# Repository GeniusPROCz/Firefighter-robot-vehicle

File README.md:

🧑‍🚒 Firefighter Robot Vehicle

Autor / Author: Jan Suttner (alias GeniusPROCz)
Rok / Year: © 2025
Verze licence / License Version: 1.0 — Custom Non-Commercial License

🛡️ Právní upozornění / Legal Notice

Tento projekt, včetně všech svých současných i budoucích částí (software, firmware, schémata, návrhy PCB, 3D modely, dokumentace, texty a obrázky), je chráněn autorským právem podle zákona č. 121/2000 Sb. (CZ) a mezinárodních úmluv (Berne Convention).
Použitím, kopírováním, úpravou nebo sdílením tohoto díla souhlasíš s níže uvedenými licenčními podmínkami.
Pokud s nimi nesouhlasíš, nemáš právo projekt nebo jeho části jakkoli používat, upravovat ani šířit.

📘 Tento projekt podléhá licenčním podmínkám uvedeným v sekci „📜 Licenční podmínky / License & Usage Terms“ níže.

📜 Licenční podmínky / License & Usage Terms

Autor / Author: Jan Suttner (GeniusPROCz)
Projekt / Project: Firefighter Robot Vehicle
Licence / License: Custom Non-Commercial License
Komerční použití / Commercial Use: Pouze po písemné dohodě s autorem / Only with author’s written consent

🇨🇿 Česká verze (právně závazná v ČR)

Autor uděluje uživatelům následující oprávnění:

✅ Povolené použití

Používat, upravovat a sdílet tento projekt pro osobní, vzdělávací a nekomerční účely.

Prezentovat nebo forkovat projekt za předpokladu zachování uvedení autora:

© 2025 Jan Suttner (GeniusPROCz) — originální projekt: https://github.com/GeniusPROCz/Firefighter-Robot-Vehicle

🚫 Zakázané použití

Jakékoli komerční využití (prodej, výroba, reklama, monetizace, placené služby atd.) bez písemného souhlasu autora.

Přivlastnění si autorství, úprava či odstranění označení původního autora.

Šíření bez tohoto licenčního textu nebo bez odkazu na původní repozitář.

⚙️ Shrnutí práv
Právo	Stav
Osobní / vzdělávací použití	✅ Povoleno
Úpravy a sdílení (s uvedením autora)	✅ Povoleno
Komerční použití	⚠️ Pouze po písemné dohodě s autorem
Přivlastnění / šíření bez zdroje	❌ Zakázáno
⚠️ Prohlášení

Projekt je poskytován „tak, jak je“ (as is) bez jakékoli záruky. Autor nenese odpovědnost za škody vzniklé použitím nebo modifikací materiálů.

🇬🇧 English Version (internationally equivalent)

The author grants the following permissions:

✅ Allowed

Use, modify and share this project for personal, educational and non-commercial purposes.

Publicly present or fork this repository with proper credit to the author:

© 2025 Jan Suttner (GeniusPROCz) — original project: https://github.com/GeniusPROCz/Firefighter-Robot-Vehicle

🚫 Prohibited

Any commercial use (sales, production, advertising, monetization, paid services, etc.) without prior written consent from the author.

Removing or altering author attribution.

Redistributing this work without this license text or a link to the original repository.

⚙️ Rights Summary
Right	Status
Personal / educational use	✅ Allowed
Modification & redistribution (with credit)	✅ Allowed
Commercial use	⚠️ Only with written permission
Misattribution / uncredited redistribution	❌ Forbidden
⚠️ Disclaimer

This project is provided “as is”, without any warranty of any kind. The author shall not be liable for any damages arising from use or modification.

✅ Použitím tohoto repozitáře výslovně souhlasíš s výše uvedenými podmínkami.
Jakékoli komerční použití bez souhlasu autora může být považováno za porušení autorských práv (§ 12 a násl. zákona č. 121/2000 Sb.).

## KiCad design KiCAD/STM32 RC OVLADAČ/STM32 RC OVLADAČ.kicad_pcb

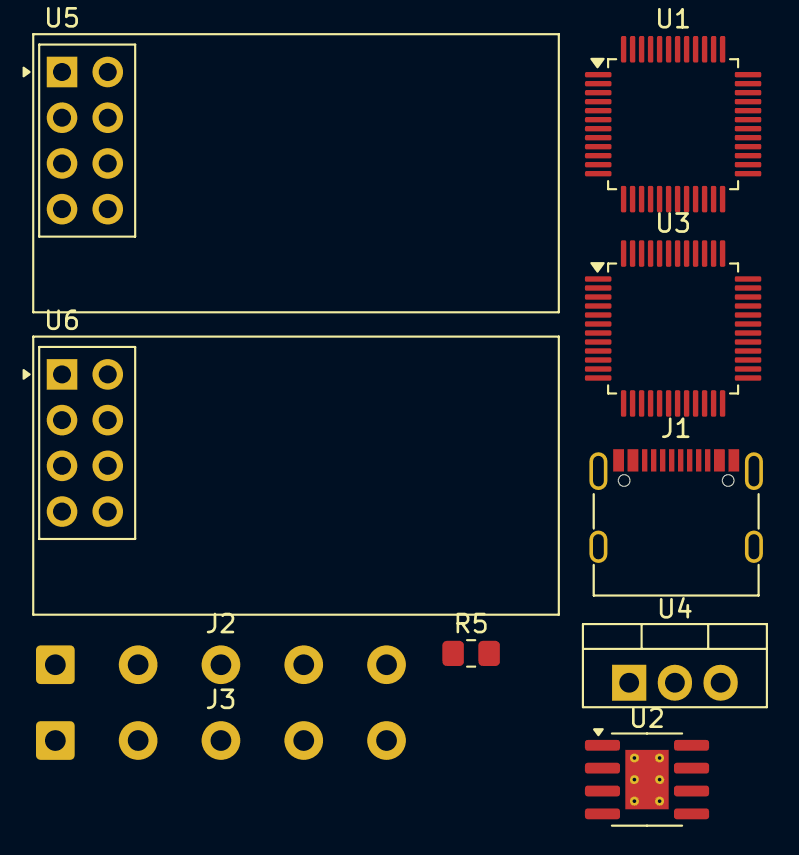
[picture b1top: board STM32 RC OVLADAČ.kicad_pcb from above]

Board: 2 copper layers, 10 parts (0 on the bottom side), 7 nets, no tracks yet.

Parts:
J1: USB_C_Receptacle_USB2.0_16P; USB_C_Receptacle_G-Switch_GT-USB-7010ASV_model
J2, J3: Conn_01x05_Socket; SolderWire-0.5sqmm_1x05_P4.6mm_D0.9mm_OD2.1mm
R5: R; R_0805_2012Metric_Pad1.20x1.40mm_HandSolder
U1, U3: STM32F030C8Tx; LQFP-48_7x7mm_P0.5mm
U2: TP4056-42-ESOP8; SOIC-8-1EP_3.9x4.9mm_P1.27mm_EP2.41x3.3mm_ThermalVias_model
U4: LD1117V33; TO-220-3_Vertical
U5, U6: NRF24L01_Breakout; nRF24L01_Breakout

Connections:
+3.3V: U1.1 (VDD), U1.9 (VDDA), U1.24 (VDD), U1.48 (VDD), U3.1 (VDD), U3.24 (VDD), U3.48 (VDD), U4.2 (VO), U5.2 (VCC), U6.2 (VCC)
GND: J1.A1 (GND), J1.A12 (GND), J1.B1 (GND), J1.B12 (GND), J1.S1 (SHIELD), J2.5, J3.5, R5.2, U1.8 (VSSA), U1.23 (VSS), U1.47 (VSS), U2.1 (TEMP), U2.3 (GND), U2.9 (EPAD), U3.23 (VSS), U3.47 (VSS), U4.1 (GND), U5.1 (GND), U6.1 (GND)
unnamed: U2.5 (BAT), U4.3 (VI)
unnamed: J1.A4 (VBUS), J1.A9 (VBUS), J1.B4 (VBUS), J1.B9 (VBUS), U2.4 (V_{CC}), U2.8 (CE)
unnamed: U1.13 (PA3), U5.3 (CE)
unnamed: R5.1, U2.2 (PROG)
unnamed: U3.13 (PA3), U6.3 (CE)

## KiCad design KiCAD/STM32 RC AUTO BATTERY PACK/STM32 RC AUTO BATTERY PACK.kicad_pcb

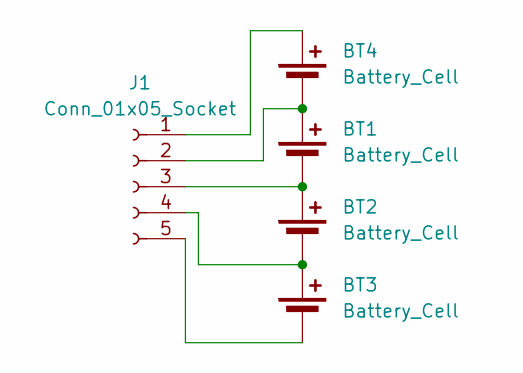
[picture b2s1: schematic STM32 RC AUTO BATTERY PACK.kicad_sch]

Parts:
BT1, BT2, BT3, BT4: Battery_Cell; 21700 laskakit battery holder
J1: Conn_01x05_Socket; JST_XH_B5B-XH-A_1x05_P2.50mm_Vertical

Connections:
unnamed: BT1.1 (+), BT4.2 (-), J1.2
unnamed: BT1.2 (-), BT2.1 (+), J1.3
unnamed: BT2.2 (-), BT3.1 (+), J1.4
unnamed: BT3.2 (-), J1.5
unnamed: BT4.1 (+), J1.1

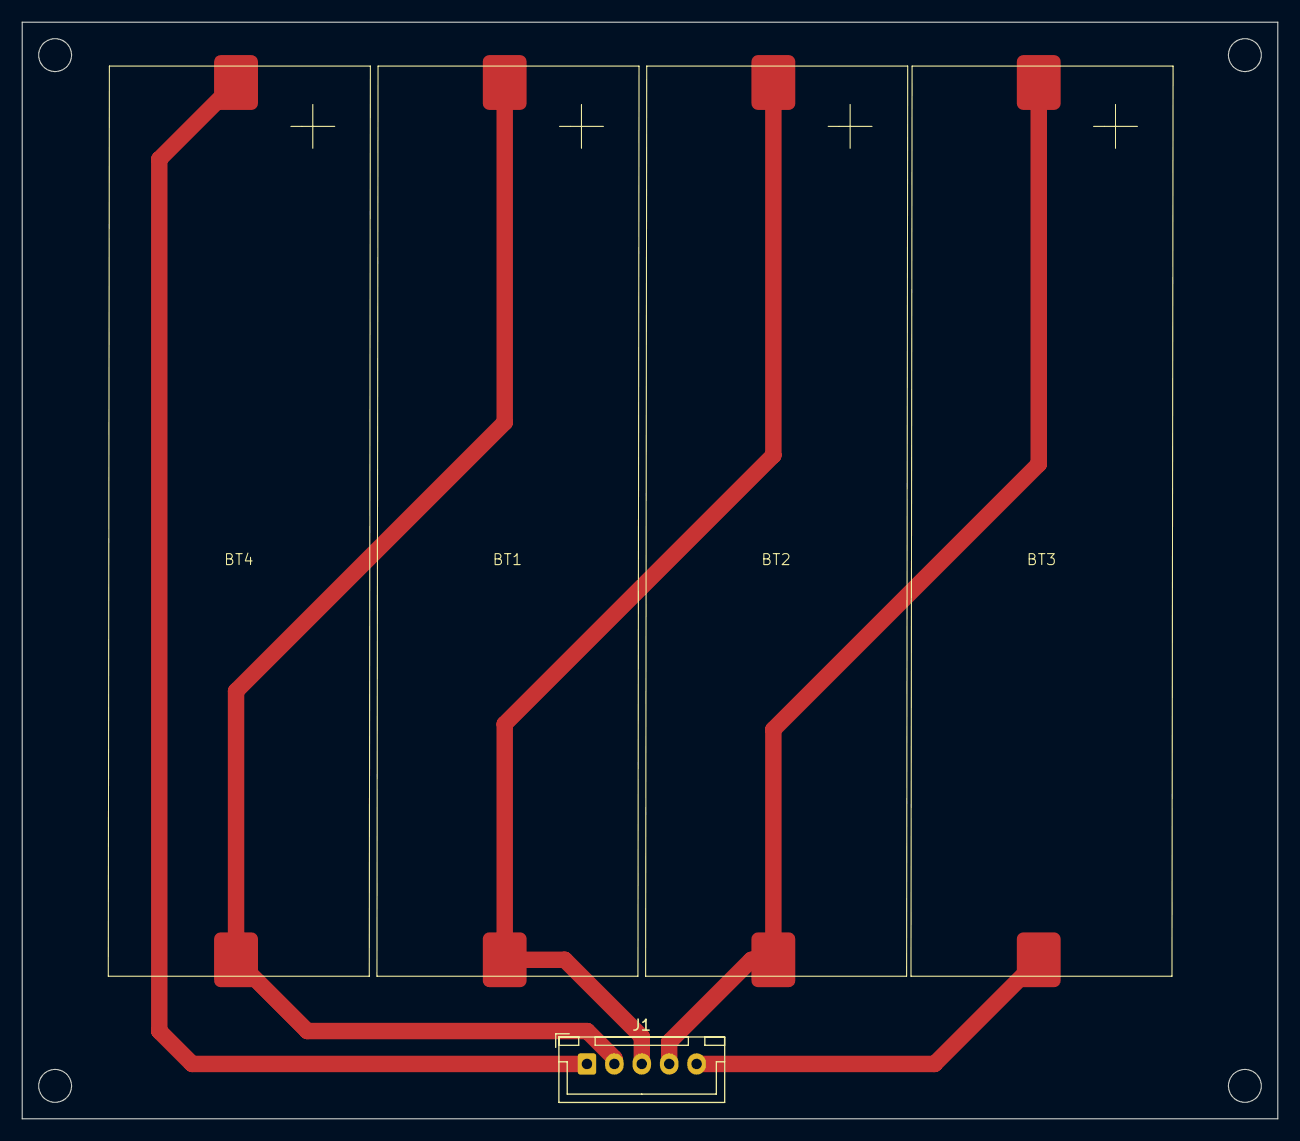
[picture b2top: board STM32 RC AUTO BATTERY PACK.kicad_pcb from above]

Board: 2 copper layers, 114.5 x 100.0 mm, 5 parts (0 on the bottom side), 5 nets.

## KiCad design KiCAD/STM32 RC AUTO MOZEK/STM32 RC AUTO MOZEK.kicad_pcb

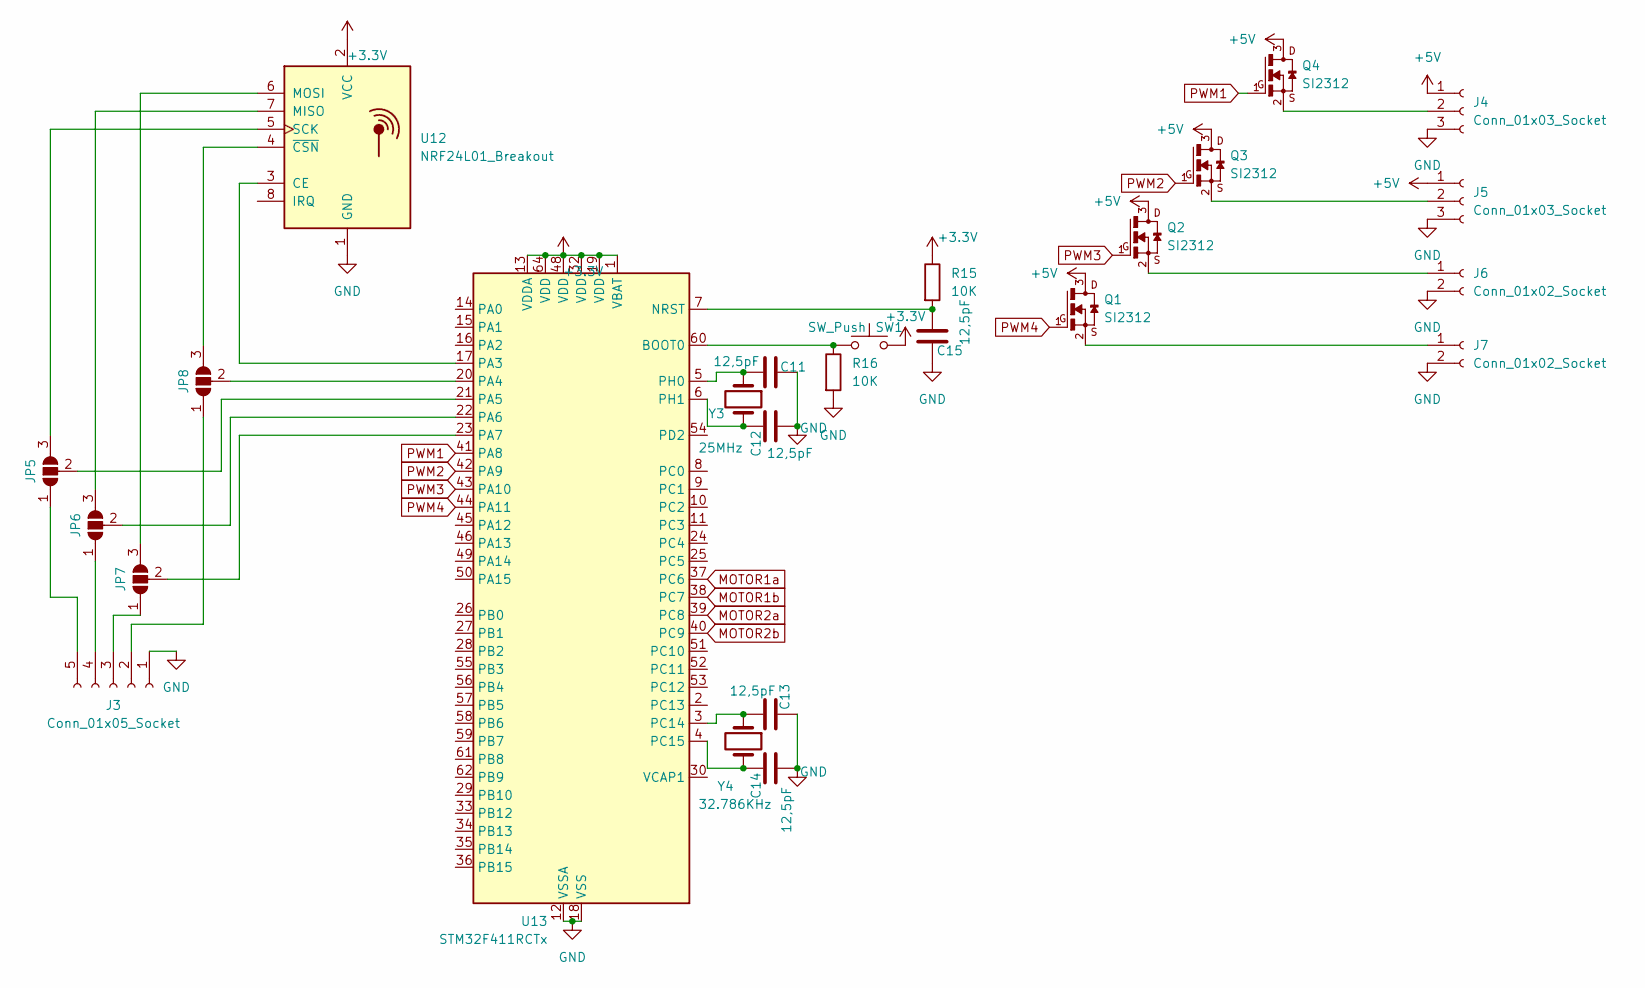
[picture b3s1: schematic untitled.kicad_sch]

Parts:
C11, C12, C13, C14, C15: 12,5pF; C_0805_2012Metric_Pad1.18x1.45mm_HandSolder
J3: Conn_01x05_Socket; SolderWire-0.5sqmm_1x05_P4.8mm_D0.9mm_OD2.3mm_Relief
J4, J5: Conn_01x03_Socket; JST_XH_B3B-XH-A_1x03_P2.50mm_Vertical
J6, J7: Conn_01x02_Socket; JST_XH_B2B-XH-A_1x02_P2.50mm_Vertical
JP5, JP6, JP7, JP8: SolderJumper_3_Open; SolderJumper-3_P1.3mm_Open_RoundedPad1.0x1.5mm_NumberLabels
Q1, Q2, Q3, Q4: SI2312; SOT23
R15, R16: 10K; R_0805_2012Metric_Pad1.20x1.40mm_HandSolder
SW1: SW_Push; SW_SPST_CK_RS282G05A3
U12: NRF24L01_Breakout; nRF24L01_Breakout
U13: STM32F411RCTx; LQFP-64_10x10mm_P0.5mm
Y3: 25MHz; Crystal_SMD_HC49-SD
Y4: 32.786KHz; Crystal_DS26_D2.0mm_L6.0mm_Horizontal

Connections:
+3.3V: R15.1, SW1.2, U12.2 (VCC), U13.1 (VBAT), U13.13 (VDDA), U13.19 (VDD), U13.32 (VDD), U13.48 (VDD), U13.64 (VDD); also elsewhere on the board
+5V: J4.1, J5.1, Q1.3, Q2.3, Q3.3, Q4.3; also elsewhere on the board
GND: C11.1, C12.2, C13.1, C14.2, C15.1, J3.1, J4.3, J5.3, J6.2, J7.2, R16.2, U12.1 (GND), U13.12 (VSSA), U13.18 (VSS), U13.31 (VSS), U13.47 (VSS), U13.63 (VSS); also elsewhere on the board
MOTOR1a: U13.37 (PC6); also elsewhere on the board
MOTOR1b: U13.38 (PC7); also elsewhere on the board
MOTOR2a: U13.39 (PC8); also elsewhere on the board
MOTOR2b: U13.40 (PC9); also elsewhere on the board
unnamed: J3.2, JP8.1 (A)
unnamed: J3.3, JP7.1 (A)
unnamed: J3.4, JP6.1 (A)
unnamed: J3.5, JP5.1 (A)
unnamed: J4.2, Q4.2
unnamed: J5.2, Q3.2
unnamed: J6.1, Q2.2
unnamed: J7.1, Q1.2
unnamed: JP5.3 (B), U12.5 (SCK)
unnamed: JP5.2 (C), U13.21 (PA5)
unnamed: JP6.3 (B), U12.7 (MISO)
unnamed: JP6.2 (C), U13.22 (PA6)
unnamed: JP7.3 (B), U12.6 (MOSI)
unnamed: JP7.2 (C), U13.23 (PA7)
unnamed: JP8.3 (B), U12.4 (~CSN)
unnamed: JP8.2 (C), U13.20 (PA4)
unnamed: U12.3 (CE), U13.17 (PA3)
unnamed: R16.1, SW1.1, U13.60 (BOOT0)
unnamed: C15.2, R15.2, U13.7 (NRST)
unnamed: C13.2, U13.3 (PC14), Y4.1
unnamed: C14.1, U13.4 (PC15), Y4.2
unnamed: C11.2, U13.5 (PH0), Y3.1
unnamed: C12.1, U13.6 (PH1), Y3.2
PWM1: Q4.1, U13.41 (PA8)
PWM2: Q3.1, U13.42 (PA9)
PWM3: Q2.1, U13.43 (PA10)
PWM4: Q1.1, U13.44 (PA11)

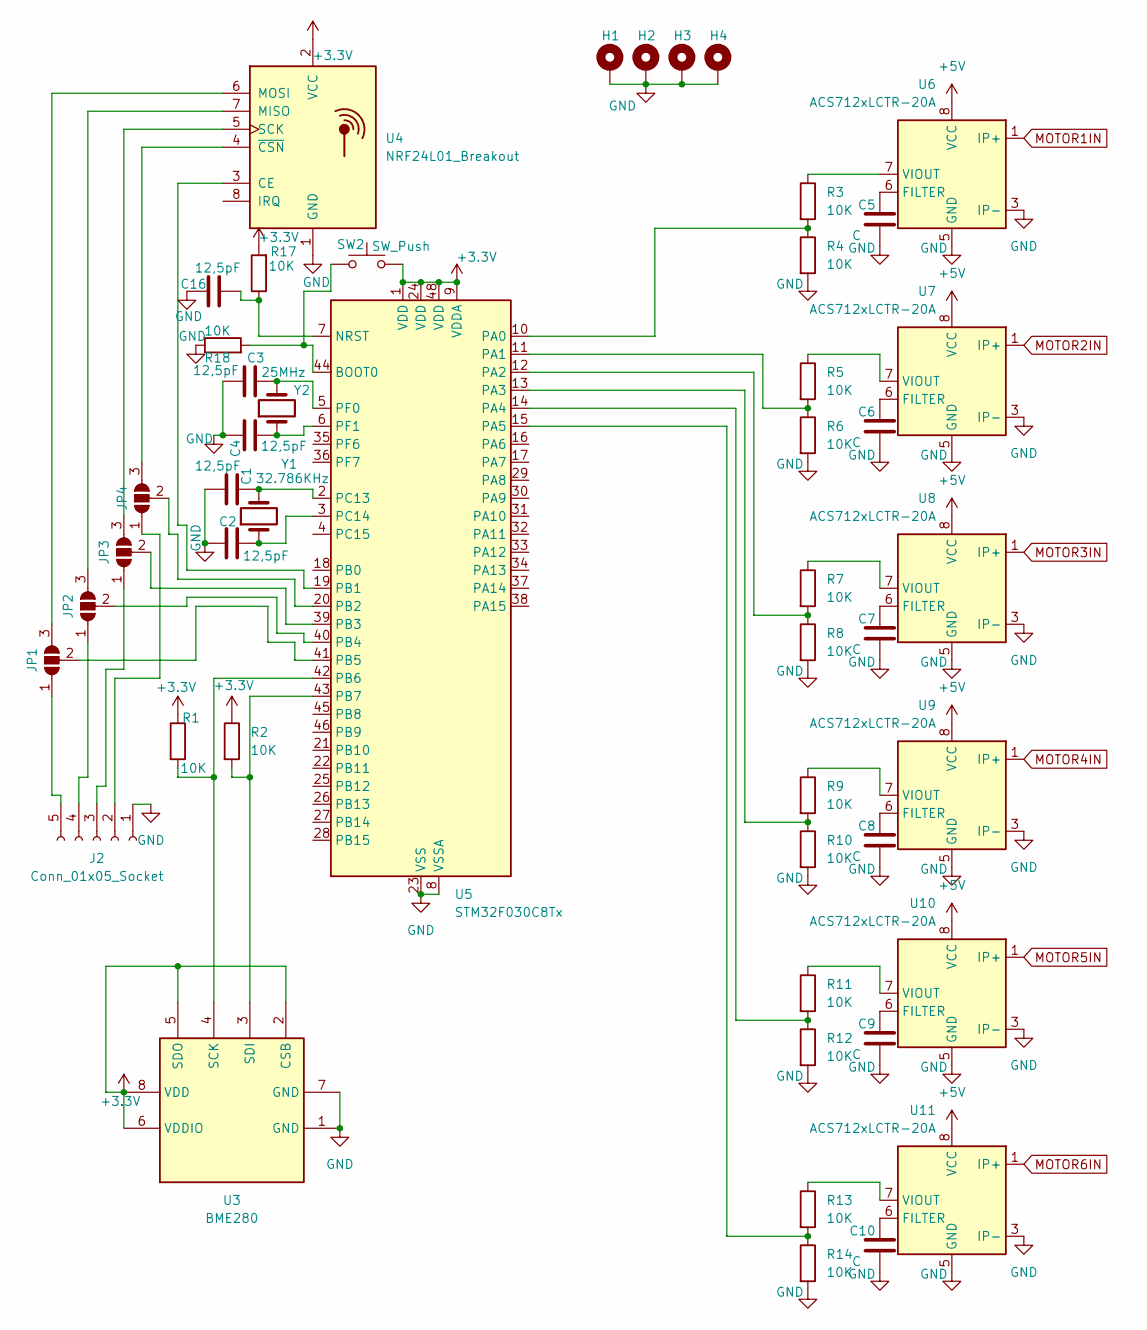
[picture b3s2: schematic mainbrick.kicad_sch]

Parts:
C1, C2, C3, C4, C16: 12,5pF; C_0805_2012Metric_Pad1.18x1.45mm_HandSolder
C5, C6, C7, C8, C9, C10: C; C_0805_2012Metric_Pad1.18x1.45mm_HandSolder
H1, H2, H3, H4: MountingHole_Pad; MountingHole_3.5mm_Pad_Via
J2: Conn_01x05_Socket; SolderWire-0.5sqmm_1x05_P4.8mm_D0.9mm_OD2.3mm_Relief
JP1, JP2, JP3, JP4: SolderJumper_3_Open; SolderJumper-3_P1.3mm_Open_RoundedPad1.0x1.5mm_NumberLabels
R1, R2, R3, R4, R5, R6, R7, R8, R9, R10, R11, R12, R13, R14, R17, R18: 10K; R_0805_2012Metric_Pad1.20x1.40mm_HandSolder
SW2: SW_Push; SW_SPST_CK_RS282G05A3
U3: BME280; Bosch_LGA-8_2.5x2.5mm_P0.65mm_ClockwisePinNumbering
U4: NRF24L01_Breakout; nRF24L01_Breakout
U5: STM32F030C8Tx; LQFP-48_7x7mm_P0.5mm
U6, U7, U8, U9, U10, U11: ACS712xLCTR-20A; SOIC-8_3.9x4.9mm_P1.27mm
Y1: 32.786KHz; Crystal_DS26_D2.0mm_L6.0mm_Horizontal
Y2: 25MHz; Crystal_SMD_HC49-SD

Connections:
+3.3V: R1.1, R2.1, R17.2, SW2.2, U3.2 (CSB), U3.5 (SDO), U3.6 (VDDIO), U3.8 (VDD), U4.2 (VCC), U5.1 (VDD), U5.9 (VDDA), U5.24 (VDD), U5.48 (VDD); also elsewhere on the board
+5V: U6.8 (VCC), U7.8 (VCC), U8.8 (VCC), U9.8 (VCC), U10.8 (VCC), U11.8 (VCC); also elsewhere on the board
GND: C1.2, C2.1, C3.2, C4.1, C5.2, C6.2, C7.2, C8.2, C9.2, C10.2, C16.2, H1.1, H2.1, H3.1, H4.1, J2.1, R4.2, R6.2, R8.2, R10.2, R12.2, R14.2, R18.1, U3.1 (GND), U3.7 (GND), U4.1 (GND), U5.8 (VSSA), U5.23 (VSS), U5.47 (VSS), U6.3 (IP-), U6.4 (IP-), U6.5 (GND), U7.3 (IP-), U7.4 (IP-), U7.5 (GND), U8.3 (IP-), U8.4 (IP-), U8.5 (GND), U9.3 (IP-), U9.4 (IP-), U9.5 (GND), U10.3 (IP-), U10.4 (IP-), U10.5 (GND), U11.3 (IP-), U11.4 (IP-), U11.5 (GND); also elsewhere on the board
MOTOR1IN: U6.1 (IP+), U6.2 (IP+); also elsewhere on the board
MOTOR2IN: U7.1 (IP+), U7.2 (IP+); also elsewhere on the board
MOTOR3IN: U8.1 (IP+), U8.2 (IP+); also elsewhere on the board
MOTOR4IN: U9.1 (IP+), U9.2 (IP+); also elsewhere on the board
MOTOR5IN: U10.1 (IP+), U10.2 (IP+); also elsewhere on the board
MOTOR6IN: U11.1 (IP+), U11.2 (IP+); also elsewhere on the board
unnamed: J2.2, JP4.1 (A)
unnamed: J2.3, JP3.1 (A)
unnamed: J2.4, JP2.1 (A)
unnamed: J2.5, JP1.1 (A)
unnamed: JP1.3 (B), U4.6 (MOSI)
unnamed: JP1.2 (C), U5.41 (PB5)
unnamed: JP2.3 (B), U4.7 (MISO)
unnamed: JP2.2 (C), U5.40 (PB4)
unnamed: JP3.3 (B), U4.5 (SCK)
unnamed: JP3.2 (C), U5.39 (PB3)
unnamed: JP4.3 (B), U4.4 (~CSN)
unnamed: JP4.2 (C), U5.20 (PB2)
unnamed: R1.2, U3.4 (SCK), U5.42 (PB6)
unnamed: R2.2, U3.3 (SDI), U5.43 (PB7)
unnamed: U4.3 (CE), U5.19 (PB1)
unnamed: R18.2, SW2.1, U5.44 (BOOT0)
unnamed: C16.1, R17.1, U5.7 (NRST)
unnamed: R3.2, R4.1, U5.10 (PA0)
unnamed: R5.2, R6.1, U5.11 (PA1)
unnamed: R7.2, R8.1, U5.12 (PA2)
unnamed: R9.2, R10.1, U5.13 (PA3)
unnamed: R11.2, R12.1, U5.14 (PA4)
unnamed: R13.2, R14.1, U5.15 (PA5)
unnamed: C1.1, U5.2 (PC13), Y1.2
unnamed: C2.2, U5.3 (PC14), Y1.1
unnamed: C3.1, U5.5 (PF0), Y2.2
unnamed: C4.2, U5.6 (PF1), Y2.1
unnamed: C5.1, U6.6 (FILTER)
unnamed: R3.1, U6.7 (VIOUT)
unnamed: C6.1, U7.6 (FILTER)
unnamed: R5.1, U7.7 (VIOUT)
unnamed: C7.1, U8.6 (FILTER)
unnamed: R7.1, U8.7 (VIOUT)
unnamed: C8.1, U9.6 (FILTER)
unnamed: R9.1, U9.7 (VIOUT)
unnamed: C9.1, U10.6 (FILTER)
unnamed: R11.1, U10.7 (VIOUT)
unnamed: C10.1, U11.6 (FILTER)
unnamed: R13.1, U11.7 (VIOUT)

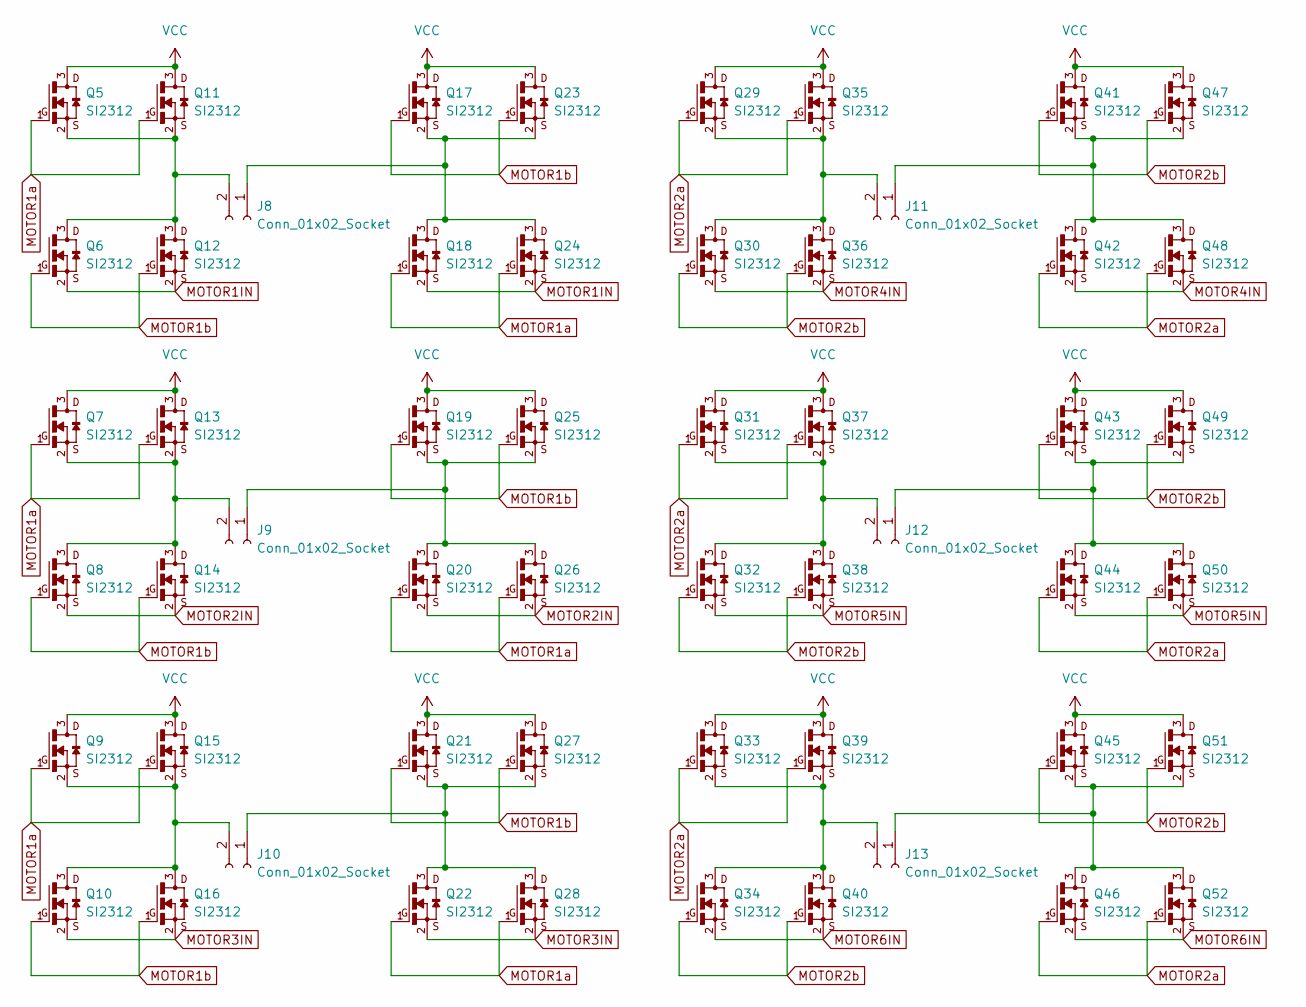
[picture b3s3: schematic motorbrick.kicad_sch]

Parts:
J8, J9, J10, J11, J12, J13: Conn_01x02_Socket; SolderWire-2sqmm_1x02_P7.8mm_D2mm_OD3.9mm
Q5, Q6, Q7, Q8, Q9, Q10, Q11, Q12, Q13, Q14, Q15, Q16, Q17, Q18, Q19, Q20, Q21, Q22, Q23, Q24, Q25, Q26, Q27, Q28, Q29, Q30, Q31, Q32, Q33, Q34, Q35, Q36, Q37, Q38, Q39, Q40, Q41, Q42, Q43, Q44, Q45, Q46, Q47, Q48, Q49, Q50, Q51, Q52: SI2312; SOT23

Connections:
MOTOR1IN: Q6.2, Q12.2, Q18.2, Q24.2; also elsewhere on the board
MOTOR1a: Q5.1, Q7.1, Q9.1, Q11.1, Q13.1, Q15.1, Q18.1, Q20.1, Q22.1, Q24.1, Q26.1, Q28.1; also elsewhere on the board
MOTOR1b: Q6.1, Q8.1, Q10.1, Q12.1, Q14.1, Q16.1, Q17.1, Q19.1, Q21.1, Q23.1, Q25.1, Q27.1; also elsewhere on the board
MOTOR2IN: Q8.2, Q14.2, Q20.2, Q26.2; also elsewhere on the board
MOTOR2a: Q29.1, Q31.1, Q33.1, Q35.1, Q37.1, Q39.1, Q42.1, Q44.1, Q46.1, Q48.1, Q50.1, Q52.1; also elsewhere on the board
MOTOR2b: Q30.1, Q32.1, Q34.1, Q36.1, Q38.1, Q40.1, Q41.1, Q43.1, Q45.1, Q47.1, Q49.1, Q51.1; also elsewhere on the board
MOTOR3IN: Q10.2, Q16.2, Q22.2, Q28.2; also elsewhere on the board
MOTOR4IN: Q30.2, Q36.2, Q42.2, Q48.2; also elsewhere on the board
MOTOR5IN: Q32.2, Q38.2, Q44.2, Q50.2; also elsewhere on the board
MOTOR6IN: Q34.2, Q40.2, Q46.2, Q52.2; also elsewhere on the board
unnamed: J8.1, Q17.2, Q18.3, Q23.2, Q24.3
unnamed: J8.2, Q5.2, Q6.3, Q11.2, Q12.3
unnamed: J9.1, Q19.2, Q20.3, Q25.2, Q26.3
unnamed: J9.2, Q7.2, Q8.3, Q13.2, Q14.3
unnamed: J10.1, Q21.2, Q22.3, Q27.2, Q28.3
unnamed: J10.2, Q9.2, Q10.3, Q15.2, Q16.3
unnamed: J11.1, Q41.2, Q42.3, Q47.2, Q48.3
unnamed: J11.2, Q29.2, Q30.3, Q35.2, Q36.3
unnamed: J12.1, Q43.2, Q44.3, Q49.2, Q50.3
unnamed: J12.2, Q31.2, Q32.3, Q37.2, Q38.3
unnamed: J13.1, Q45.2, Q46.3, Q51.2, Q52.3
unnamed: J13.2, Q33.2, Q34.3, Q39.2, Q40.3
VCC: Q5.3, Q7.3, Q9.3, Q11.3, Q13.3, Q15.3, Q17.3, Q19.3, Q21.3, Q23.3, Q25.3, Q27.3, Q29.3, Q31.3, Q33.3, Q35.3, Q37.3, Q39.3, Q41.3, Q43.3, Q45.3, Q47.3, Q49.3, Q51.3; also elsewhere on the board

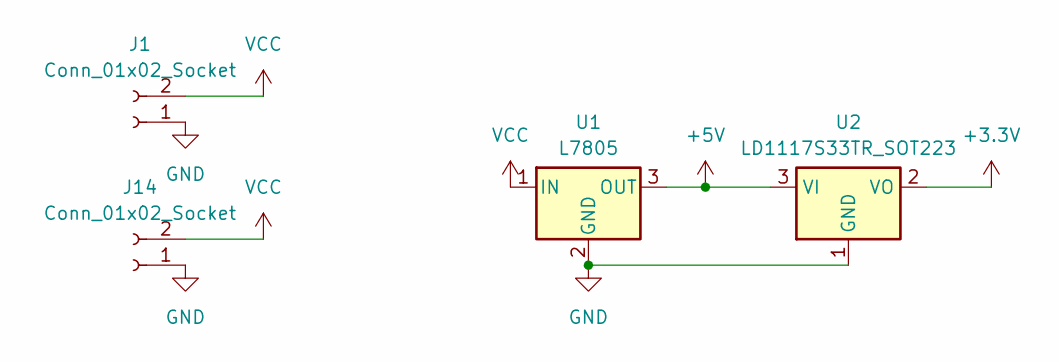
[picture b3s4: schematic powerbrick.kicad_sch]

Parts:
J1, J14: Conn_01x02_Socket; SolderWire-2sqmm_1x02_P7.8mm_D2mm_OD3.9mm
U1: L7805; TO-220-3_Horizontal_TabDown
U2: LD1117S33TR_SOT223; SOT-223-3_TabPin2

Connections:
+3.3V: U2.2 (VO); also elsewhere on the board
+5V: U1.3 (OUT), U2.3 (VI); also elsewhere on the board
GND: J1.1, J14.1, U1.2 (GND), U2.1 (GND); also elsewhere on the board
VCC: J1.2, J14.2, U1.1 (IN); also elsewhere on the board

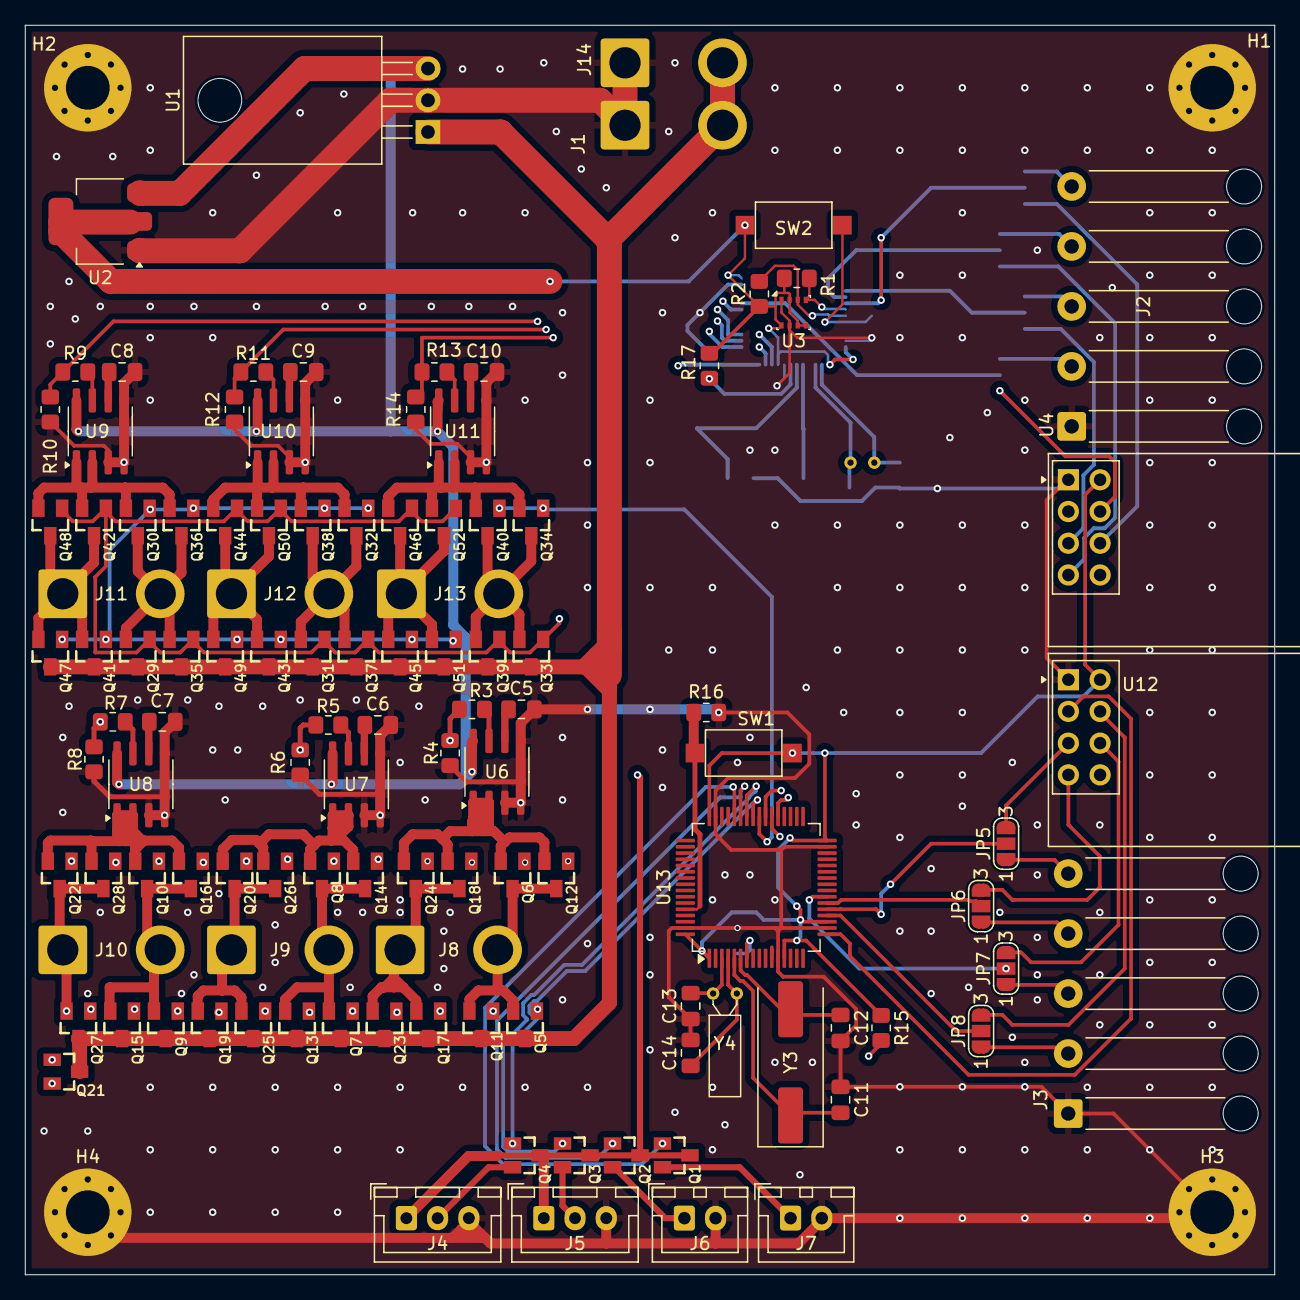
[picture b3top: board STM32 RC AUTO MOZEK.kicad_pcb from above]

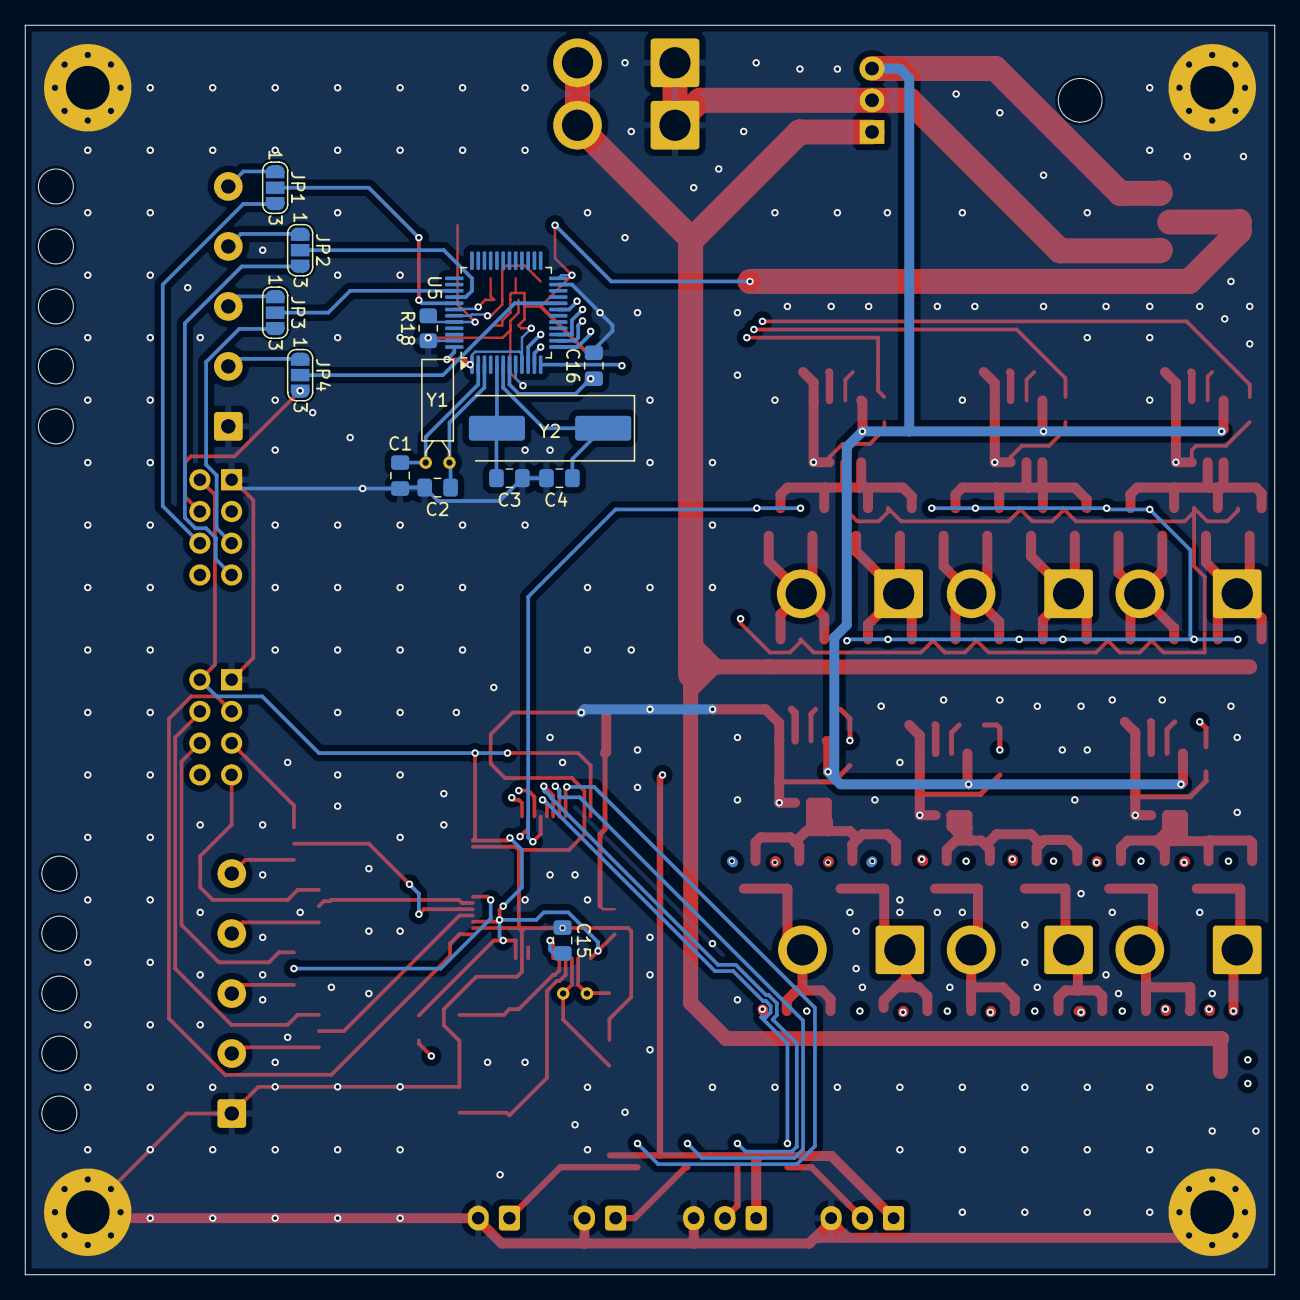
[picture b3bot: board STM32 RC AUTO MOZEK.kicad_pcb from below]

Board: 4 copper layers, 100.0 x 100.0 mm, 131 parts (14 on the bottom side), 92 nets.

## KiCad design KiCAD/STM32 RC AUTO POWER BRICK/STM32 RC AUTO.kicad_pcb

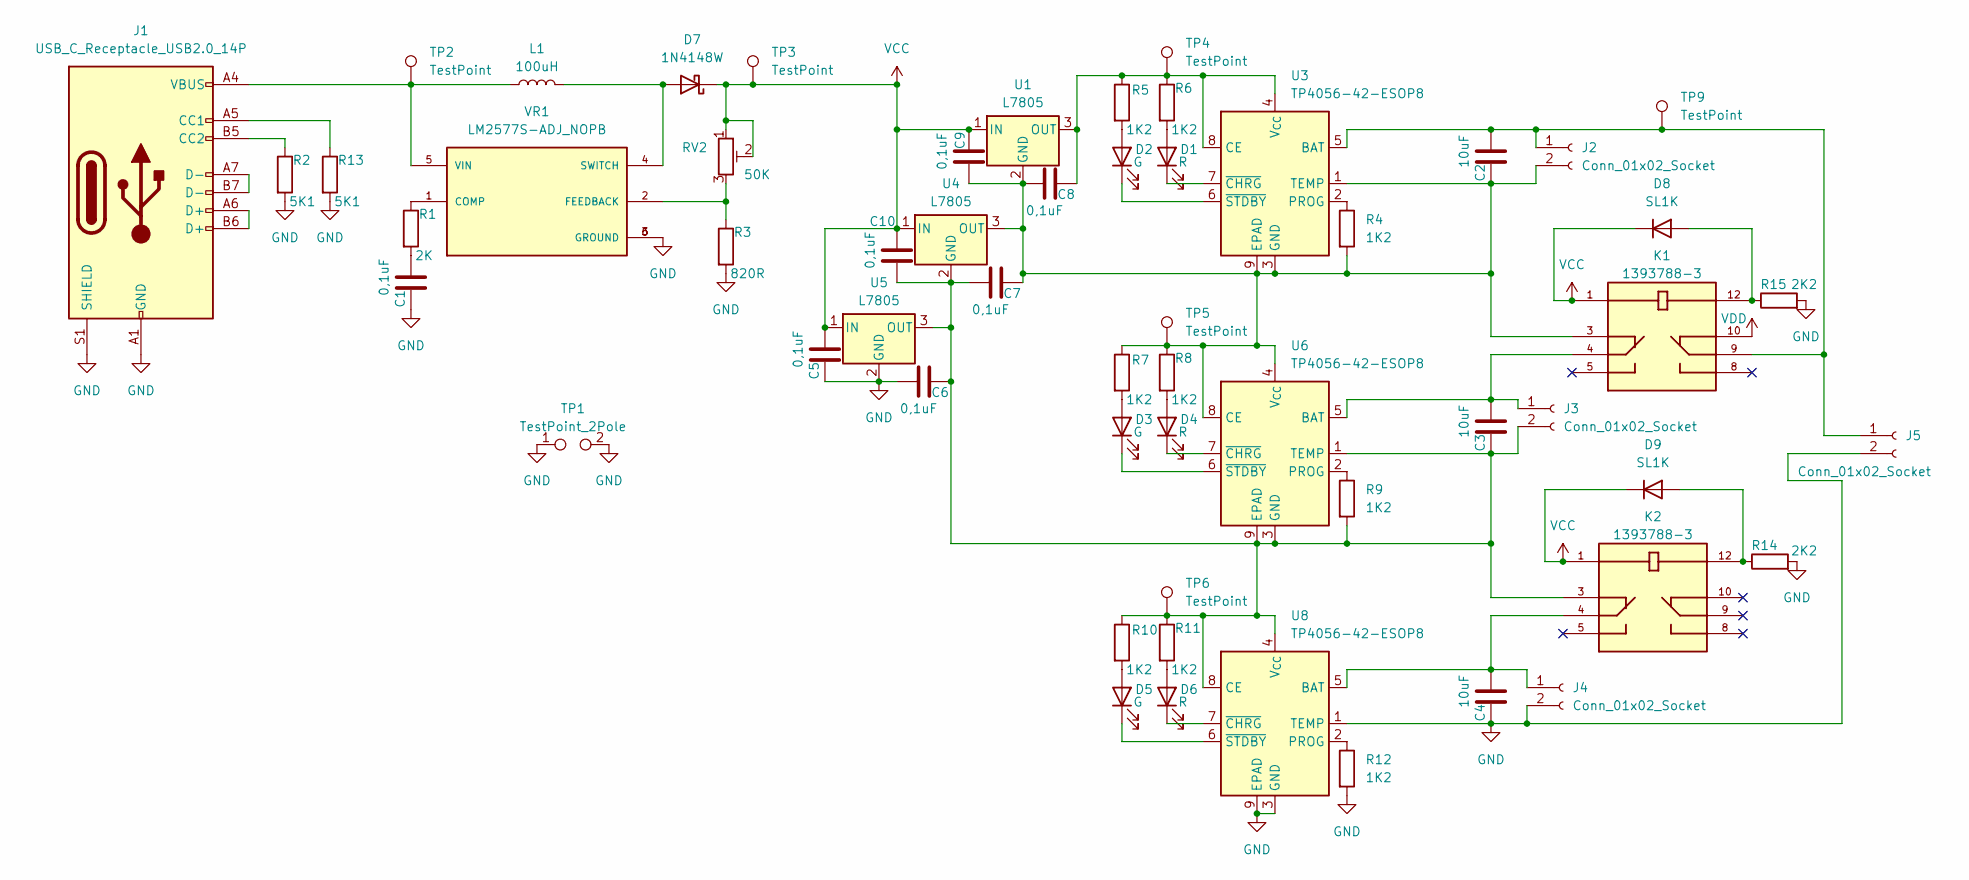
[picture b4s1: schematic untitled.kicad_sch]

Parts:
C1, C5, C6, C7, C8, C9, C10: 0,1uF; C_0603_1608Metric_Pad1.08x0.95mm_HandSolder
C2, C3, C4: 10uF; C_0603_1608Metric_Pad1.08x0.95mm_HandSolder
D1, D4, D6: R; LED_0603_1608Metric_Pad1.05x0.95mm_HandSolder
D2, D3, D5: G; LED_0603_1608Metric_Pad1.05x0.95mm_HandSolder
D7: 1N4148W; D_SOD-123F
D8, D9: SL1K; D_SOD-123F
J1: USB_C_Receptacle_USB2.0_14P; USB_C_Receptacle_G-Switch_GT-USB-7010ASV_model
J2, J3, J4, J5: Conn_01x02_Socket; JST_XH_B2B-XH-A_1x02_P2.50mm_Vertical
K1, K2: 1393788-3; TE_1393788-3_model
L1: 100uH; L_12x12mm_H4.5mm_model
R1: 2K; R_0603_1608Metric_Pad0.98x0.95mm_HandSolder
R2, R13: 5K1; R_0603_1608Metric_Pad0.98x0.95mm_HandSolder
R3: 820R; R_0603_1608Metric_Pad0.98x0.95mm_HandSolder
R4, R5, R6, R7, R8, R9, R10, R11, R12: 1K2; R_0603_1608Metric_Pad0.98x0.95mm_HandSolder
R14, R15: 2K2; R_0603_1608Metric_Pad0.98x0.95mm_HandSolder
RV2: 50K; Potentiometer_ACP_CA6-VSMD_Vertical_model
TP1: TestPoint_2Pole; TestPoint_2Pads_Pitch2.54mm_Drill0.8mm
TP2, TP3, TP4, TP5, TP6, TP9: TestPoint; TestPoint_Pad_D1.5mm
U1, U4, U5: L7805; TO-252-2
U3, U6, U8: TP4056-42-ESOP8; SOIC-8-1EP_3.9x4.9mm_P1.27mm_EP2.41x3.3mm_ThermalVias_model
VR1: LM2577S-ADJ_NOPB; VREG_LM2577S-ADJ_NOPB_model; PARTREV D

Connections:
GND: C1.1, C4.1, C5.1, C6.2, J1.A1 (GND), J1.A12 (GND), J1.B1 (GND), J1.B12 (GND), J1.S1 (SHIELD), J4.2, J5.2, R2.2, R3.2, R12.2, R13.2, R14.2, R15.2, TP1.1, TP1.2, U5.2 (GND), U8.1 (TEMP), U8.3 (GND), U8.9 (EPAD), VR1.3 (GROUND), VR1.6 (GROUND)
unnamed: C1.2, R1.2
unnamed: D1.2 (A), R6.2
unnamed: D1.1 (K), U3.7 (~CHRG)
unnamed: D2.2 (A), R5.2
unnamed: D2.1 (K), U3.6 (~STDBY)
unnamed: D3.2 (A), R7.2
unnamed: D3.1 (K), U6.6 (~STDBY)
unnamed: D4.2 (A), R8.2
unnamed: D4.1 (K), U6.7 (~CHRG)
unnamed: D5.2 (A), R10.2
unnamed: D5.1 (K), U8.6 (~STDBY)
unnamed: D6.2 (A), R11.2
unnamed: D6.1 (K), U8.7 (~CHRG)
unnamed: D7.2 (A), L1.2, VR1.4 (SWITCH)
unnamed: D8.2 (A), K1.12, R15.1
unnamed: D9.2 (A), K2.12, R14.1
unnamed: J1.A5 (CC1), R13.1
unnamed: J1.B5 (CC2), R2.1
unnamed: J1.A6 (D+), J1.B6 (D+)
unnamed: J1.A7 (D-), J1.B7 (D-)
unnamed: C2.2, J2.1, J5.1, K1.9, TP9.1, U3.5 (BAT)
unnamed: C2.1, C7.1, C8.2, C9.1, J2.2, K1.3, R4.2, R7.1, R8.1, TP5.1, U1.2 (GND), U3.1 (TEMP), U3.3 (GND), U3.9 (EPAD), U4.3 (OUT), U6.4 (V_{CC}), U6.8 (CE)
unnamed: C3.2, J3.1, K1.4, U6.5 (BAT)
unnamed: C3.1, C6.1, C7.2, C10.1, J3.2, K2.3, R9.2, R10.1, R11.1, TP6.1, U4.2 (GND), U5.3 (OUT), U6.1 (TEMP), U6.3 (GND), U6.9 (EPAD), U8.4 (V_{CC}), U8.8 (CE)
unnamed: C4.2, J4.1, K2.4, U8.5 (BAT)
unnamed: C8.1, R5.1, R6.1, TP4.1, U1.3 (OUT), U3.4 (V_{CC}), U3.8 (CE)
unnamed: R4.1, U3.2 (PROG)
unnamed: R9.1, U6.2 (PROG)
unnamed: R12.1, U8.2 (PROG)
unnamed: R1.1, VR1.1 (COMP)
unnamed: R3.1, RV2.3, VR1.2 (FEEDBACK)
unnamed: J1.A4 (VBUS), J1.A9 (VBUS), J1.B4 (VBUS), J1.B9 (VBUS), L1.1, TP2.1, VR1.5 (VIN)
VCC: C5.2, C9.2, C10.2, D7.1 (K), D8.1 (K), D9.1 (K), K1.1, K2.1, RV2.1, RV2.2, TP3.1, U1.1 (IN), U4.1 (IN), U5.1 (IN)
VDD: K1.10

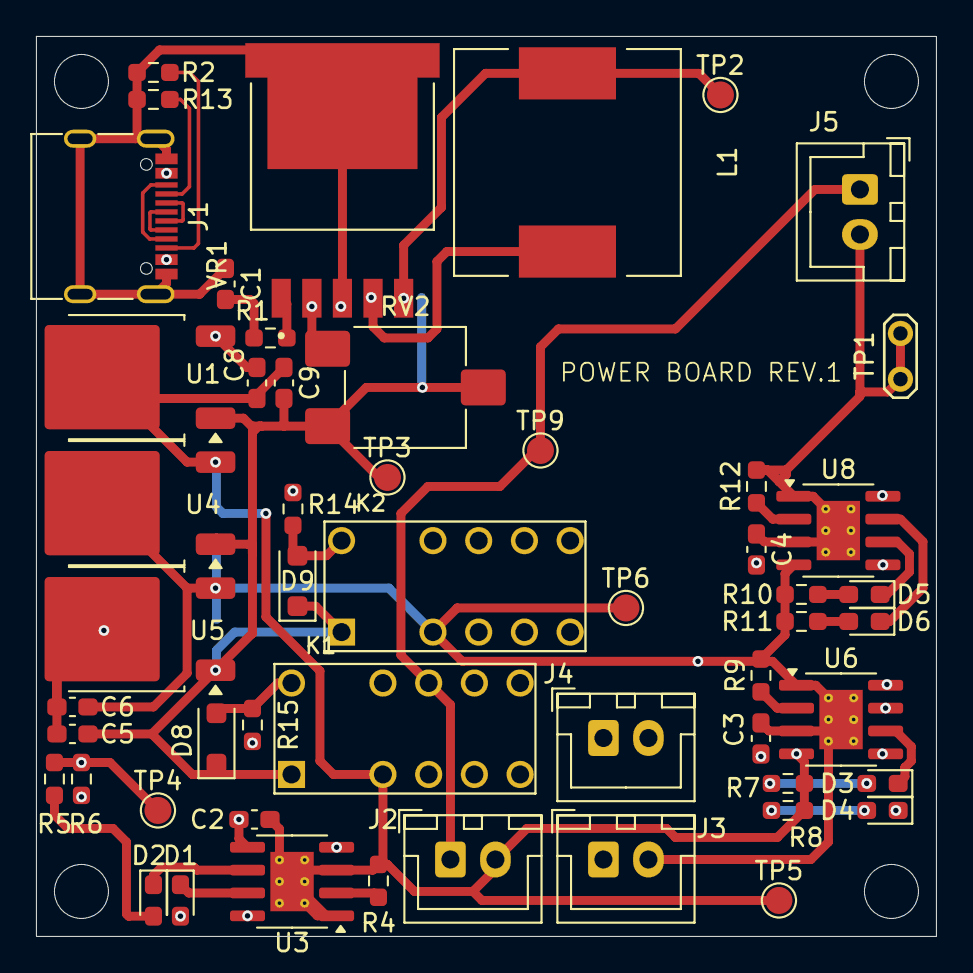
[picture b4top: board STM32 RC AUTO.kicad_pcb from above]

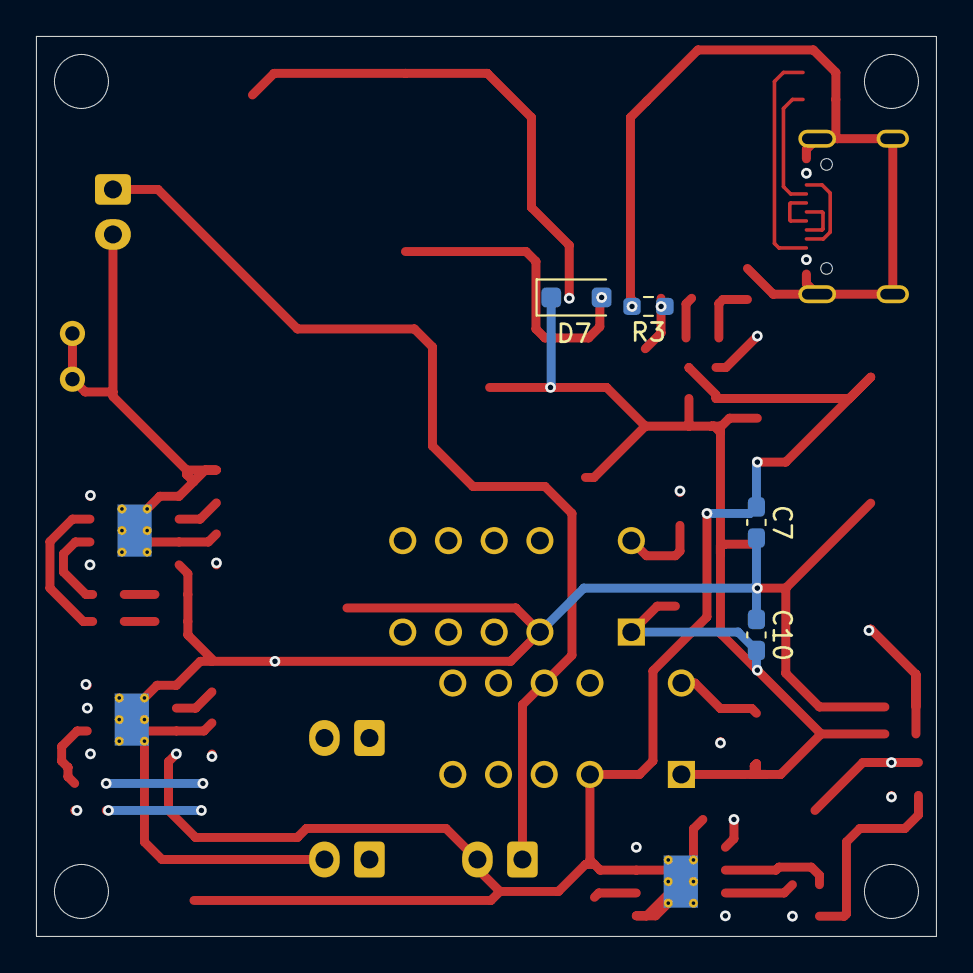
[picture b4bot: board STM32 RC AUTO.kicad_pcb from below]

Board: 4 copper layers, 50.0 x 50.0 mm, 57 parts (4 on the bottom side), 34 nets.
